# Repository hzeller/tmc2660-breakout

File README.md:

Breakout board for TMC2660
==========================

Breakout board with just the bare chip and necessary components around for
the [TMC2660][tmc2660-product] 2.8A stepper driver chip.
Detailed description found in the [datasheet][tmc2660-datasheet].

<a href="https://oshpark.com/shared_projects/CGEv10FR"></img></a>

![Rendering][rendering]

![Breakout schematic][schematic]

[tmc2660-product]: http://www.trinamic.com/products/integrated-circuits/stepper-power-driver/tmc2660
[tmc2660-datasheet]: http://www.trinamic.com/_scripts/download.php?file=_articles%2Fproducts%2Fintegrated-circuits%2Ftmc2660%2F_datasheet%2FTMC2660_datasheet.pdf
[rendering]: ./img/tmc2660-breakout.png
[schematic]: ./img/schematic.png

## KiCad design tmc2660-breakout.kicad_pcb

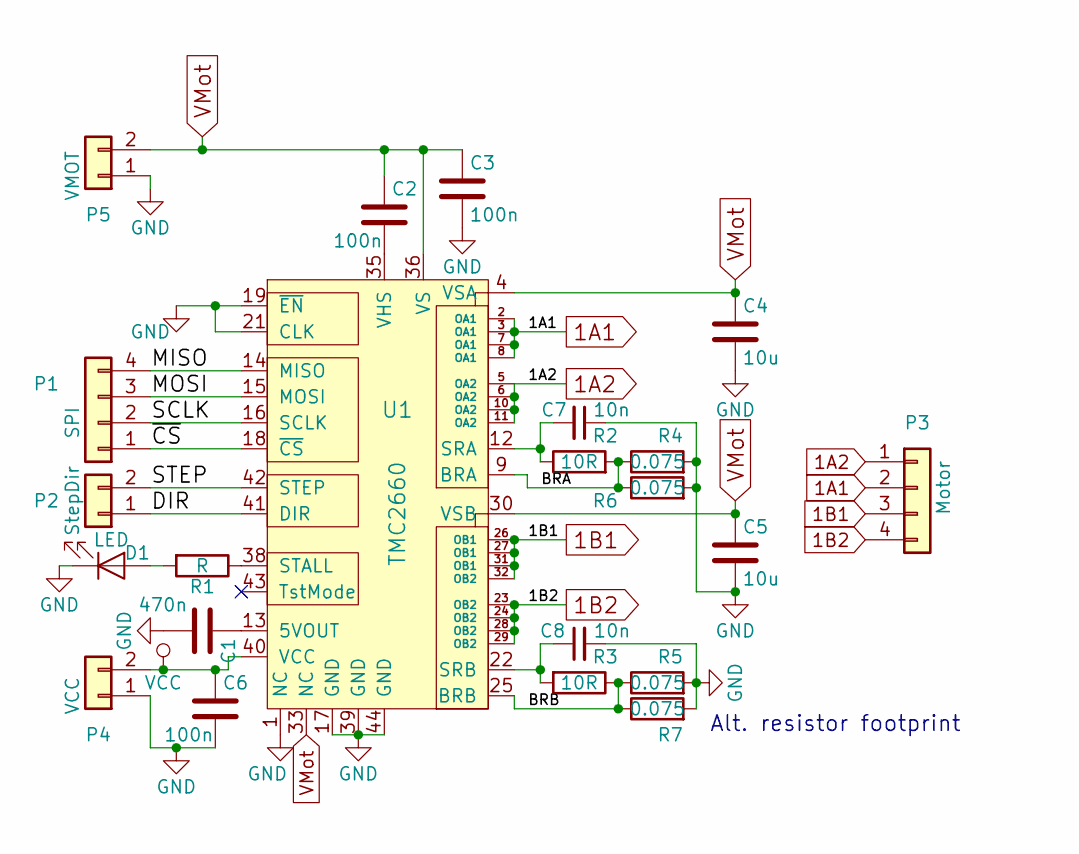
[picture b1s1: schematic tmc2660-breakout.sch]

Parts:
C1: 470n; C_0805_2012Metric
C2, C3, C6: 100n; C_0805_2012Metric
C4, C5: 10u; C_1206_3216Metric
C7, C8: 10n; C_0805_2012Metric
D1: LED; LED_0805_2012Metric
P1: SPI; PinHeader_1x04_P2.54mm_Vertical
P2: StepDir; PinHeader_1x02_P2.54mm_Vertical
P3: Motor; PinHeader_1x04_P2.54mm_Vertical
P4: VCC; PinHeader_1x02_P2.54mm_Vertical
P5: VMOT; PinHeader_1x02_P2.54mm_Vertical
R1: R; R_0805_2012Metric
R2, R3: 10R; R_0805_2012Metric
R4, R5: 0.075; R_1206_3216Metric
R6, R7: 0.075; R_2512_6332Metric
U1: TMC2660; LQFP-44_10x10mm_P0.8mm

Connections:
1A1: P3.2, U1.2 (OA1), U1.3 (OA1), U1.7 (OA1), U1.8 (OA1)
1A2: P3.1, U1.5 (OA2), U1.6 (OA2), U1.10 (OA2), U1.11 (OA2)
1B1: P3.3, U1.26 (OB1), U1.27 (OB1), U1.31 (OB1), U1.32 (OB2)
1B2: P3.4, U1.23 (OB2), U1.24 (OB2), U1.28 (OB2), U1.29 (OB2)
/BRA: R2.2, R4.1, R6.1, U1.9 (BRA)
/BRB: R3.1, R5.1, R7.1, U1.25 (BRB)
/DIR: P2.1, U1.41 (DIR)
/MISO: P1.4, U1.14 (MISO)
/MOSI: P1.3, U1.15 (MOSI)
/SCLK: P1.2, U1.16 (SCLK)
/STEP: P2.2, U1.42 (STEP)
/~CS: P1.1, U1.18 (~CS)
GND: C1.2, C3.2, C4.2, C5.2, C6.2, C7.1, C8.2, D1.1 (K), P4.1, P5.1, R4.2, R5.2, R6.2, R7.2, U1.1 (NC), U1.17 (GND), U1.19 (~EN), U1.21 (CLK), U1.39 (GND), U1.44 (GND)
unnamed: C1.1, U1.13 (5VOUT)
unnamed: C2.2, U1.35 (VHS)
unnamed: C7.2, R2.1, U1.12 (SRA)
unnamed: C8.1, R3.2, U1.22 (SRB)
unnamed: D1.2 (A), R1.2
unnamed: R1.1, U1.38 (STALL)
VCC: C6.1, P4.2, U1.40 (VCC)
VMot: C2.1, C3.1, C4.1, C5.1, P5.2, U1.4 (VSA), U1.30 (VSB), U1.33 (NC), U1.36 (VS)

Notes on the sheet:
Alt. resistor footprint

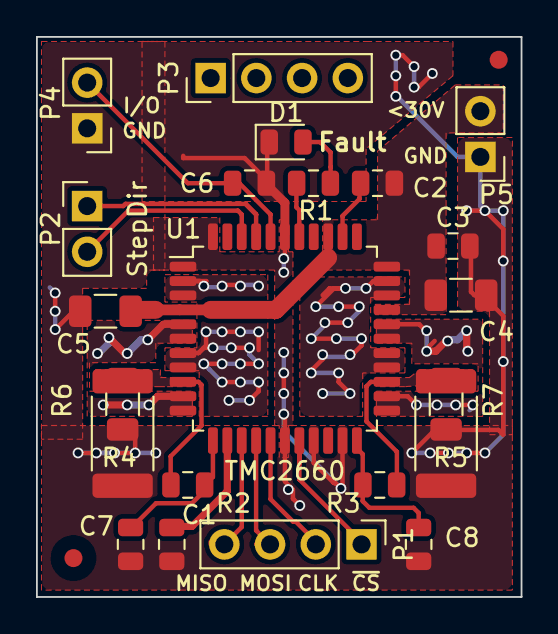
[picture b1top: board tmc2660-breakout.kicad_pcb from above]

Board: 2 copper layers, 26.9 x 31.1 mm, 22 parts (0 on the bottom side), 21 nets.

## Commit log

2015-12-14 o Start tracking.
2015-12-15 o little tweaks.
2015-12-18 o First fully placed and routed.
2015-12-18 o Add makefile to create fab files.
2015-12-18 o Better placement of git version.
2015-12-18 o Text placement tweaks.
2015-12-18 o Better labelling.
2015-12-18 o Unhide displayed signals.
2015-12-18 o Add basic readme. o Add gerbers.
2015-12-19 o More ground copper all the way around.
2015-12-19 o Top ground pin: thicker trace, now better connecting to parts of the ground plane.
2015-12-19 o Turn around VCC/GND connector so that it has the same direction as the VMOT connector. Less possibly dangerous confusion ...
2015-12-19 o Add Fiducials.
2016-01-05 o Add schematic image.
2016-01-06 o Miso/Mosi was swapped.
2016-01-07 o Add alternative footprint for shunt (2512 is more appropriate)
2016-01-07 o Widen the other 1206 pad to match the 2512 pad to avoid tombstoning
2016-01-07 o Add optional filter caps for sense input. o Connect CLK input to GND to enable internal clock. o Fix typo in sense decoupling resistor (10k -> 10R)
2016-10-28 o Update gerbers with the latest version.
2016-10-29 o Make sure that only the version of the PCB file is used to generate the git string.
2016-10-29 o Provide link to OshPark.
2016-11-13 o smallish alignments
2016-11-13 o Label some previously anonymous nets (e.g. Step/Dir).
2019-04-22 Use current KiCAD 5.x libraries.
2019-04-22 Update fab files.
2019-04-22 Crop rendering.
